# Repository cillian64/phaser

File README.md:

# phaser
Hardware device to track mains frequency and distinguish outlets on different phases

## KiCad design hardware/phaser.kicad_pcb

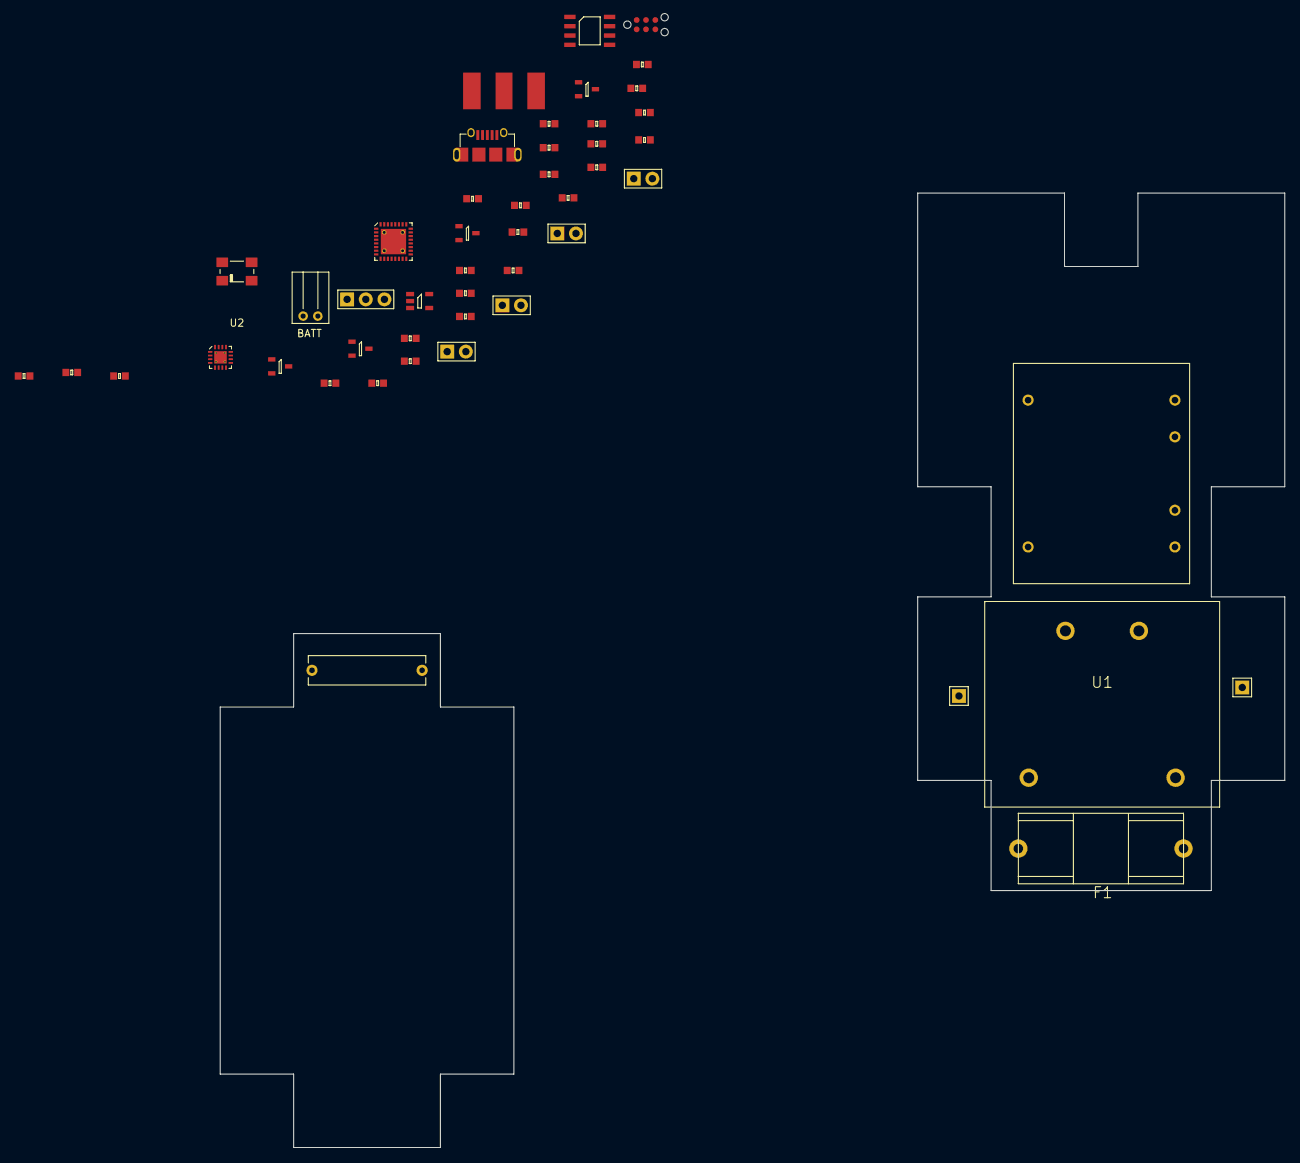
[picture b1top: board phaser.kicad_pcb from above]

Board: 2 copper layers, 145.0 x 130.0 mm, 49 parts (0 on the bottom side), 31 nets, no tracks yet.

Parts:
C1: 0.1uF/275V/X2; ECQU2A104ML
C2, C4, C5, C8: 1u; 0603
C3, C6, C10: 4u7; 0603
C7, C11, C12, C13, C14: 100n; 0603
C9: 10n; 0603
D1: RED; SIL-254P-02
D2: YELLOW; SIL-254P-02
D3: BLUE; SIL-254P-02
F1: 100mA TD; 5x20_clip
IC1: MCP1700; SOT-23
IC2: BQ24232HA; QFN-16-EP-TI
IC3: LMx93; SOIC-8
IC4: AD8541; SOT-23-5
IC5: STM32F042K4U6; QFN-32-EP-ST
J1: MICROUSB; MICROUSB_MOLEX_47589-0001
P1: L; SIL-254P-01
P2: BATT; JST-PH-2
P3: COAX; SMA-EDGE
P4: SWD_TC; TC2030-NL
P5: N; SIL-254P-01
Q1, Q2, Q3: BSS138P; SOT-23
R1: 1k8; 0603
R2, R4, R6, R7, R8, R12: 10k; 0603
R3: 45k; 0603
R5: 50k; 0603
R9, R10, R11: 68; 0603
SW1: SW; SIL-254P-02
SW2: CLK_SRC; SIL-254P-03
T1: 230/6+6 1VA; VB1.0-2-6
U1: VTX-214-003-105; VTX214
U2: FOX924B-20.000; FOX924

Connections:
+3V3: C5.1, C7.2, C8.1, C9.1, C10.1, C11.1, C12.1, C13.1, IC1.2, IC3.8, IC4.5, IC5.1, IC5.5, IC5.17, P4.1, R4.1, R7.2, R9.1, R10.1, R12.2, U2.4
/BATT_CHG: IC2.9, R4.2
/L: C1.1, F1.1, T1.1, U1.2
/N: C1.2, P5.1, T1.2, U1.1
/PUSH_SW: R12.1, SW1.1
/SWCLK: IC5.24, P4.4
/SWDIO: IC5.23, P4.2
/USB_D+: IC5.22, J1.3
/USB_D-: IC5.21, J1.2
/VSENSE: IC3.3, R5.1, R6.2
/VSENSE_REF: IC3.2, IC4.1, IC4.4, R6.1, T1.4
/nRST: C14.1, IC5.4, P4.3
GND: C2.2, C3.2, C4.2, C5.2, C6.2, C7.1, C8.2, C9.2, C10.2, C11.2, C12.2, C13.2, C14.2, IC1.1, IC2.4, IC2.5, IC2.8, IC2.EP, IC3.4, IC3.5, IC3.6, IC4.2, IC5.31, IC5.EP, J1.5, P2.2, P3.2, P4.5, Q1.2, Q2.2, Q3.2, R1.2, R2.1, R3.2, R8.1, SW1.2, U1.4, U2.2
unnamed: C2.1, IC2.13, U1.3
unnamed: C3.1, C4.1, IC1.3, IC2.6, IC2.10, IC2.11
unnamed: C6.1, IC2.2, IC2.3, P2.1
unnamed: D1.1, Q1.3
unnamed: D1.2, R9.2
unnamed: D2.1, Q2.3
unnamed: D2.2, R10.2
unnamed: D3.1, Q3.3
unnamed: D3.2, R11.2
unnamed: F1.2, P1.1
unnamed: IC2.1, R2.2
unnamed: IC2.14, R3.1
unnamed: IC2.16, R1.1
unnamed: IC4.3, R7.1, R8.2
unnamed: IC5.2, SW2.2
unnamed: P3.1, SW2.1
unnamed: R5.2, T1.3
unnamed: SW2.3, U2.3

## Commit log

2016-10-14 Add agg-kicad
2016-10-15 Finished schematic
2016-10-17 part selection
2016-10-17 Added footprints, bumped agg-kicad for bq24232
2016-11-04 Parts and rough board outlines
